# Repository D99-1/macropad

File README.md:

# An Ordinary Macropad
## What does it do you ask? Well, Macropad Stuff
### I told you, it's nothing special, just ordinary

Why press multiple keys at once on your keyboard to run a task, just bind it to one key!

Alright now you may be thinking, how was it made?

Well tbh, idk...

I was expecting it to break, and well it kinda did for the first 2 pcbs, mainly coz of my terrible soldering

But then, something happened, it finally worked

How? don't ask

All I know is that it works, and the keys are badly soldered so some are higher than others

And the thing doesn't stay flat coz the diodes are badly aligned

And a case?

well I got a 3d printer thanks to arcade... I just gotta finish the design

When will I do that?

Eventually.

Okay, thats enough yapping from me, go make your own macropad to do macropad stuff

How? Don't ask me, figure it out, make it different, better, faster, *nicely soldered*

Just have fun making it, I know for sure I did

Thats it from me, cya..

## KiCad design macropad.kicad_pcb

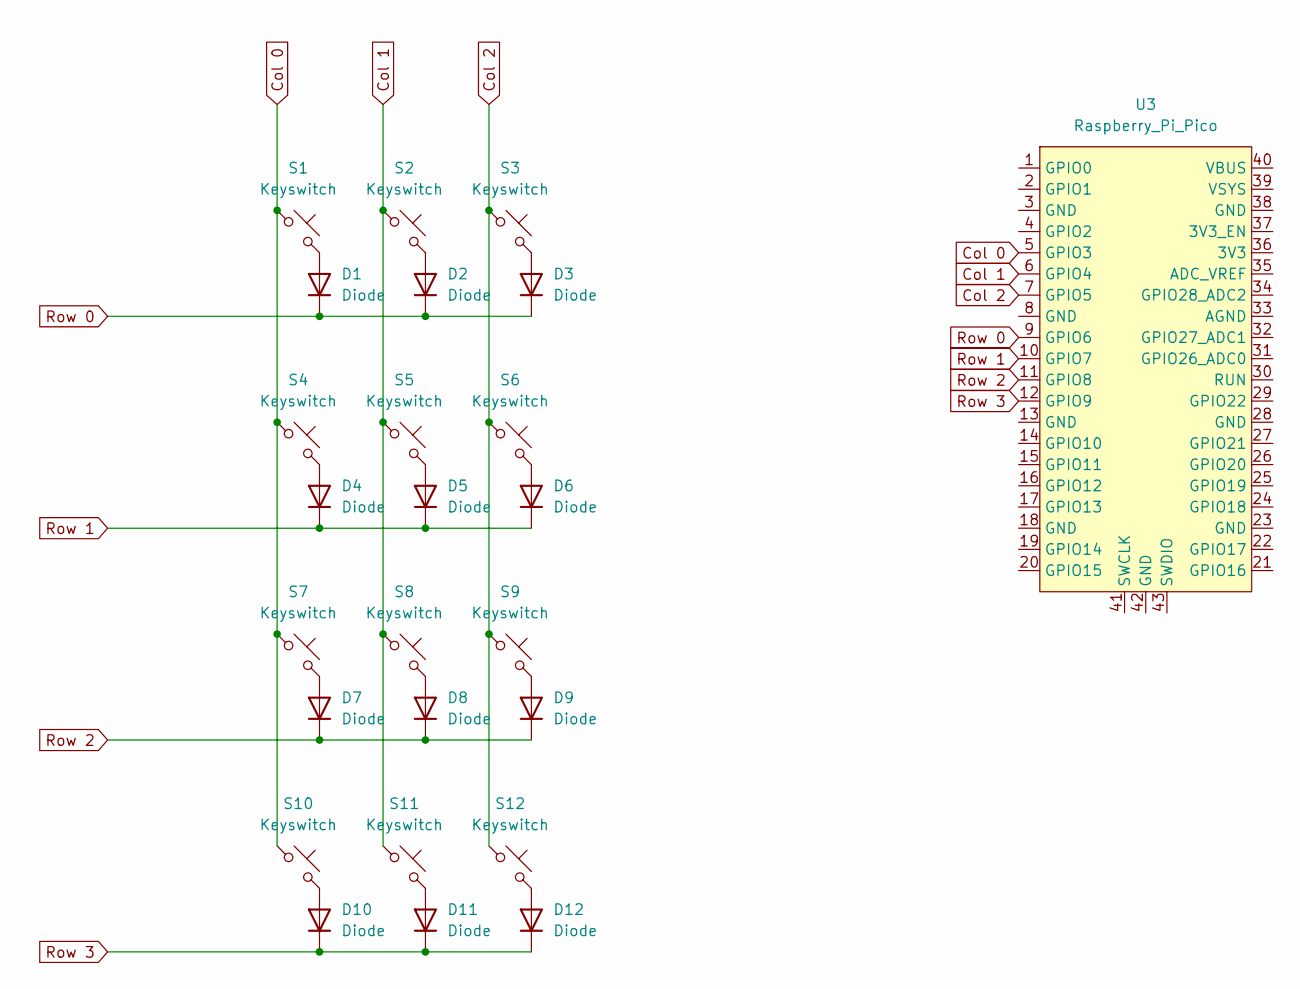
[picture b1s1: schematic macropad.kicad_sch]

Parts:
D1, D2, D3, D4, D5, D6, D7, D8, D9, D10, D11, D12: Diode; Diode_DO-35
S1, S2, S3, S4, S5, S6, S7, S8, S9, S10, S11, S12: Keyswitch; MX_PCB_1.00u
U3: Raspberry_Pi_Pico

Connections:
Col 0: S1.1, S4.1, S7.1, S10.1, U3.5 (GPIO3)
Col 1: S2.1, S5.1, S8.1, S11.1, U3.6 (GPIO4)
Col 2: S3.1, S6.1, S9.1, S12.1, U3.7 (GPIO5)
unnamed: D1.2 (A), S1.2
unnamed: D2.2 (A), S2.2
unnamed: D3.2 (A), S3.2
unnamed: D4.2 (A), S4.2
unnamed: D5.2 (A), S5.2
unnamed: D6.2 (A), S6.2
unnamed: D7.2 (A), S7.2
unnamed: D8.2 (A), S8.2
unnamed: D9.2 (A), S9.2
unnamed: D10.2 (A), S10.2
unnamed: D11.2 (A), S11.2
unnamed: D12.2 (A), S12.2
Row 0: D1.1 (K), D2.1 (K), D3.1 (K), U3.9 (GPIO6)
Row 1: D4.1 (K), D5.1 (K), D6.1 (K), U3.10 (GPIO7)
Row 2: D7.1 (K), D8.1 (K), D9.1 (K), U3.11 (GPIO8)
Row 3: D10.1 (K), D11.1 (K), D12.1 (K), U3.12 (GPIO9)

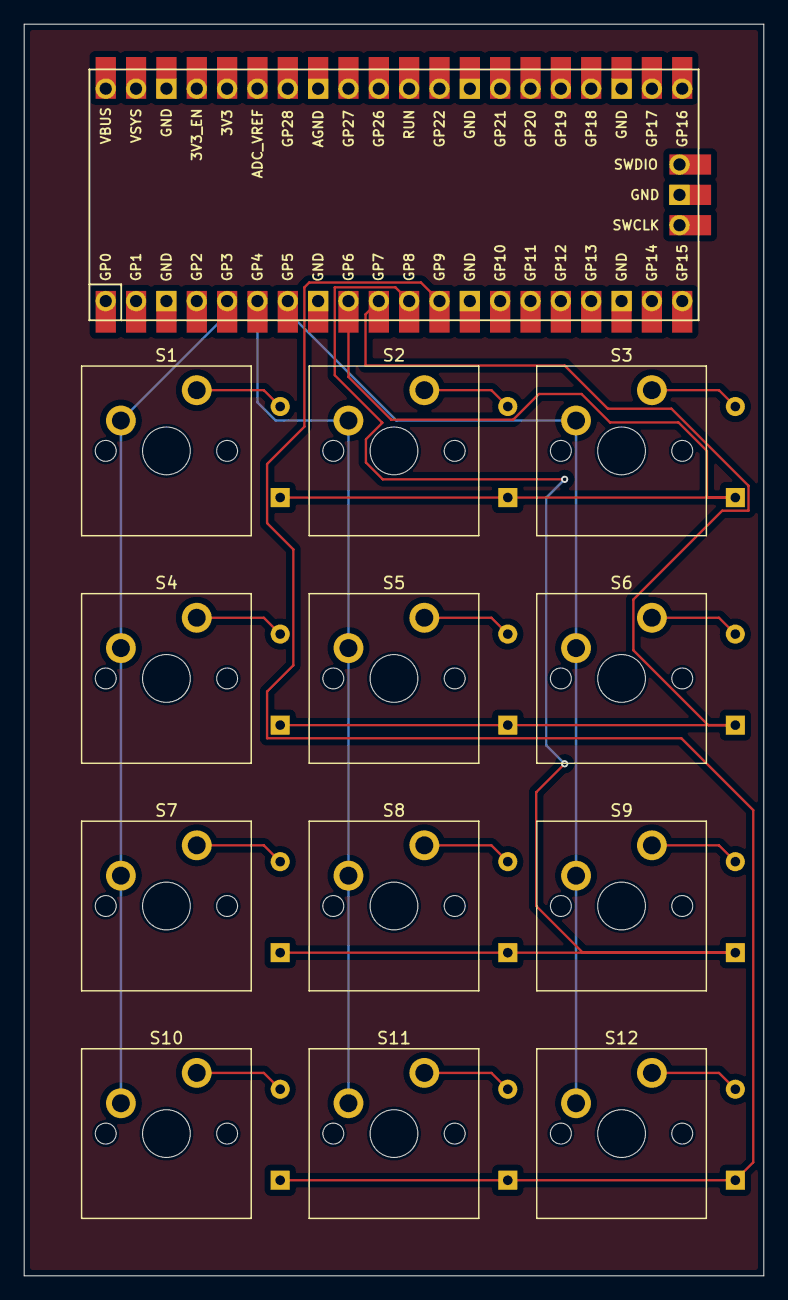
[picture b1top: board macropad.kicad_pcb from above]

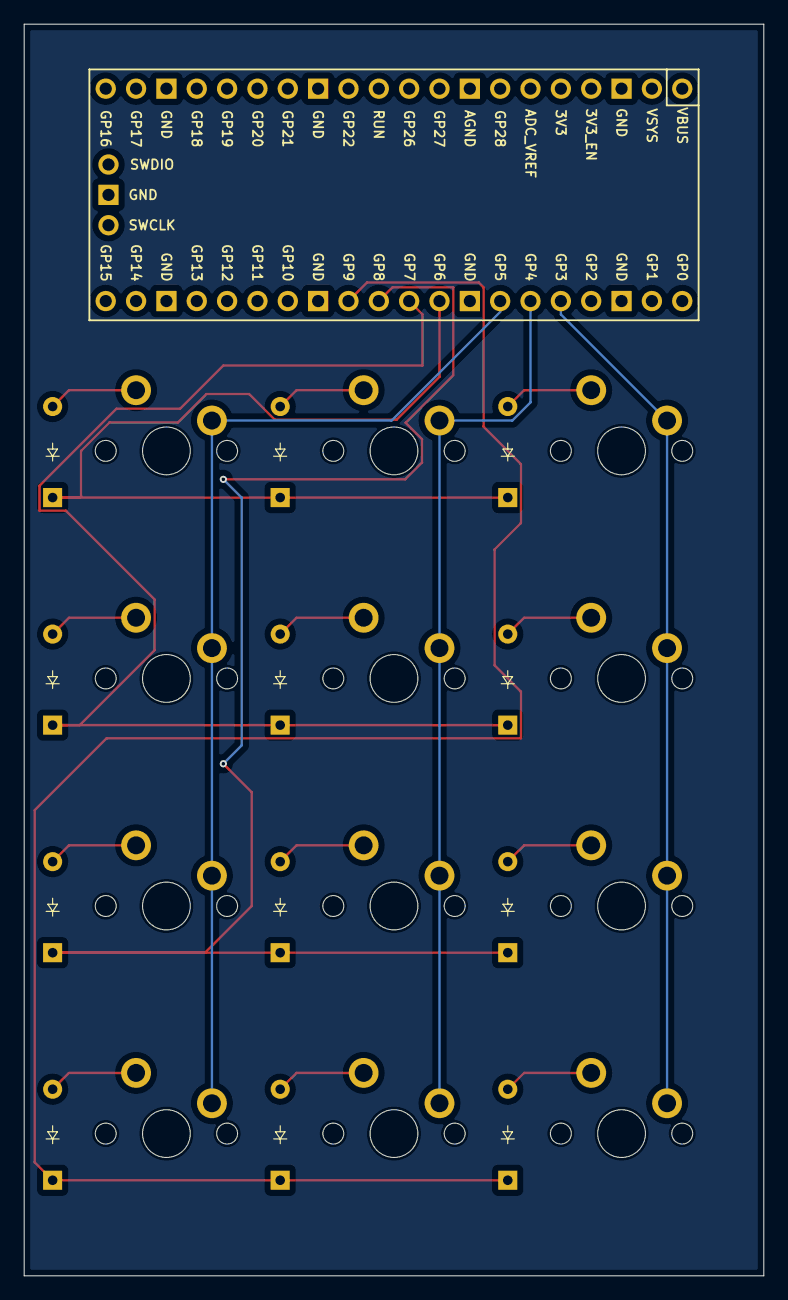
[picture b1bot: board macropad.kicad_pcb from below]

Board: 2 copper layers, 61.9 x 104.8 mm, 25 parts (12 on the bottom side), 19 nets.

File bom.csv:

Designator,Footprint,Quantity,Value,LCSC Part #
"D1, D10, D11, D12, D2, D3, D4, D5, D6, D7, D8, D9",Diode_DO-35,12,Diode,
"S1, S10, S11, S12, S2, S3, S4, S5, S6, S7, S8, S9",MX_PCB_1.00u,12,Keyswitch,
U3,Raspberry_Pi_Pico,1,Raspberry_Pi_Pico,

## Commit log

2024-07-25 Reorganise switches due to 1mm positioning error
2024-08-25 yapping
